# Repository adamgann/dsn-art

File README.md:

# dsn-art
Live wall art of spacecraft communicating over NASA's Deep Space Network. By Adam Gannon.

### Repo Structure
- `eagle/` contains PCB files for the Pi HAT in Eagle CAD
- `images/` contains spacecraft images used to make cutouts
- `python/` contains the `dsnleds` package which runs on the Pi. See README for 
code setup.

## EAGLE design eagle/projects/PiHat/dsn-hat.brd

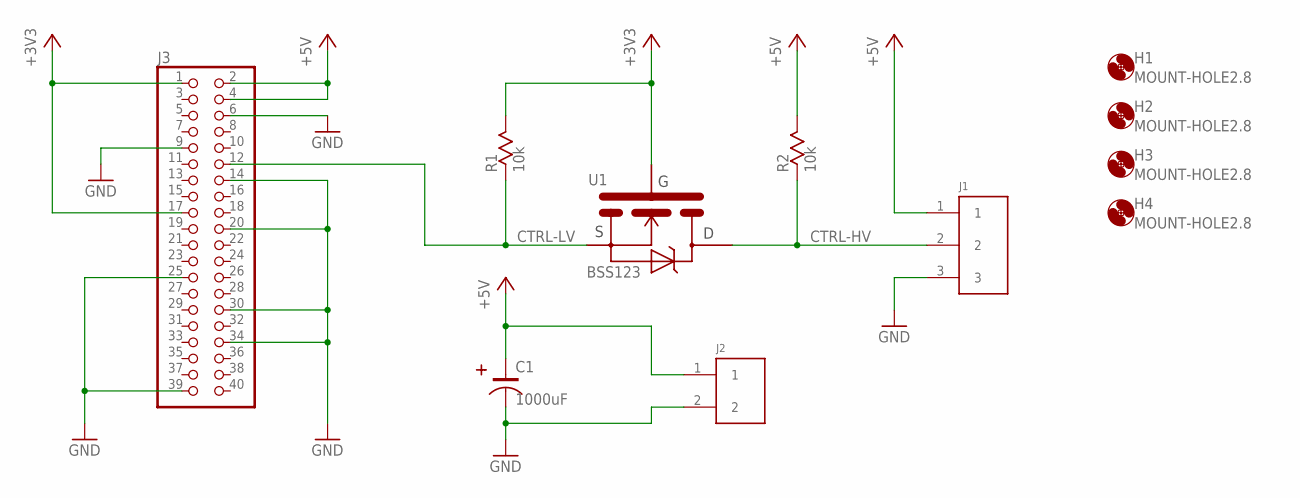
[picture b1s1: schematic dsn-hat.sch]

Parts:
C1: 1000uF; CAP-TH
H1, H2, H3, H4: MOUNT-HOLE2.8; 2,8
J1: TERM-TH-3TERM-TH-3; TERM-TH-3
J2: TERM-TH-2TH2; TERM-TH-2
J3: PINHD-2X20; 2X20
R1, R2: 10k; R0805
U1: BSS123; SOT23

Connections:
+3V3: J3.1, J3.17, R1.1, U1.1 (G)
+5V: C1.POS, J1.1, J2.1, J3.2, J3.4, R2.1
CTRL-HV: J1.2, R2.2, U1.3 (D)
CTRL-LV: J3.12, R1.2, U1.2 (S)
GND: C1.NEG, J1.3, J2.2, J3.6, J3.9, J3.14, J3.20, J3.25, J3.30, J3.34, J3.39

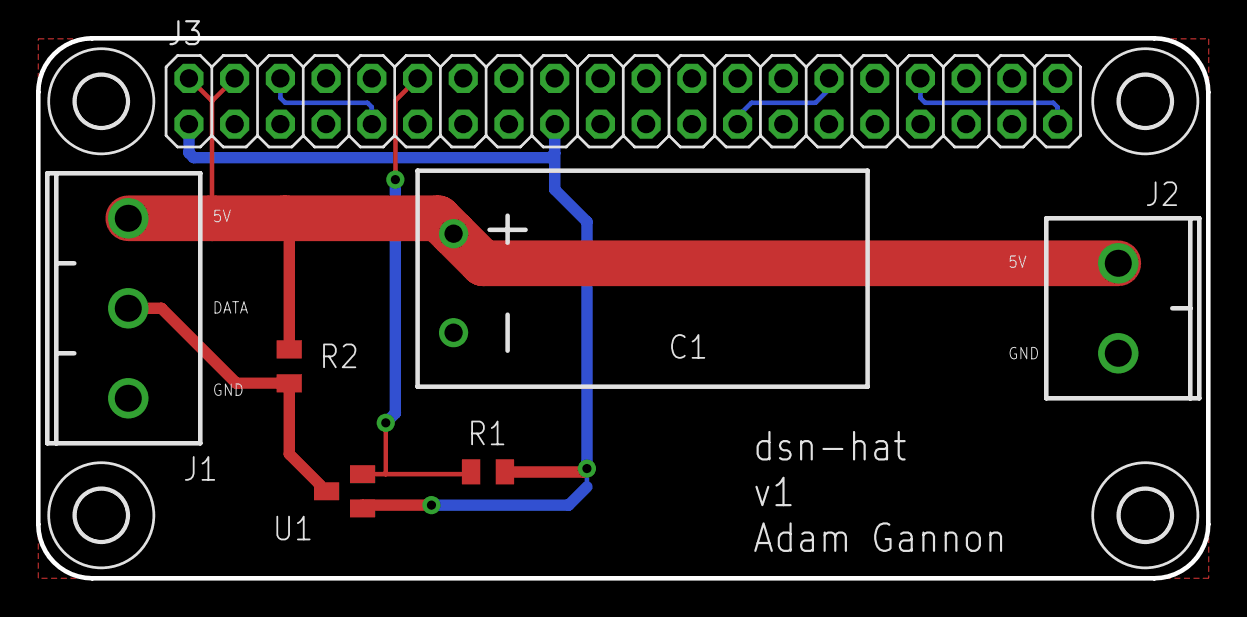
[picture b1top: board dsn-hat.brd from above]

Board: 2 copper layers, 65.0 x 30.0 mm, 11 parts (0 on the bottom side), 5 nets.

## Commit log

2021-01-10 Added prereqs and submodule ref to pydsn.
2021-01-10 Started script to test LED segments.
2021-01-16 Prelim software working.
2021-12-31 First draft of PCB in Eagle.
2023-02-05 Initial version of images.
2023-10-06 Update board files, as sent to fab shop.
2023-10-06 Updated pin map for actual hardware.
2023-10-07 Basic working.
2023-10-07 Copied over parser from pydsn and removed submodule.
2023-10-07 Reworking classes to be much cleaner.
2023-10-07 Using new classes in top-level.
2023-10-07 Better filtering logic.
2023-10-09 Logging, argparse, better lighting logic. Added time window for display.
2023-10-14 Fix LED logic.
2023-10-14 Voyager mapping.
2023-10-14 Add logging.
2023-10-14 Debugs, colors, longer default loop time.
2023-10-14 Catch kill.
2023-10-14 Remove depreciated hardware.py
2023-10-15 Turning LEDs off when outside time band.
2023-10-31 Increase loop time more.
2023-10-31 Moved to better repo structure.
2023-11-18 Update top-level README.
2023-11-18 Initial version of installable script.
2023-11-18 Fixed missing args
2023-11-18 Updated dependencies.
2023-11-18 Remove depreciated gitmodules.
2023-11-18 Added test script that randomly lights LEDs for offline demo.
